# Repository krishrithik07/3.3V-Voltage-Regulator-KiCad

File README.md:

# 3.3V Voltage Regulator Circuit

**KiCad | AP2112K-3.3 | Power Supply Design**

## Project Overview

This project involves designing a 3.3V voltage regulator circuit using the AP2112K-3.3 Low Dropout (LDO) regulator.

The circuit schematic includes input and output capacitors for power supply filtering and stable voltage regulation.

## Main Component

- AP2112K-3.3 – 3.3V LDO Voltage Regulator
- Input capacitors
- Output capacitors
- Power input and output connections

## Design Tools

- KiCad – Schematic Capture
- KiCad PCB Editor – PCB Layout (if completed)

## Design Progress

- [x] Schematic design
- [ ] Electrical Rule Check (ERC)
- [ ] Footprint assignment
- [ ] PCB layout
- [ ] Design Rule Check (DRC)
- [ ] Gerber generation
- [ ] Hardware testing

## Author

**Krishna Raj M**

Electronics and Communication Engineering

**Project Category:** PCB Design | Power Electronics

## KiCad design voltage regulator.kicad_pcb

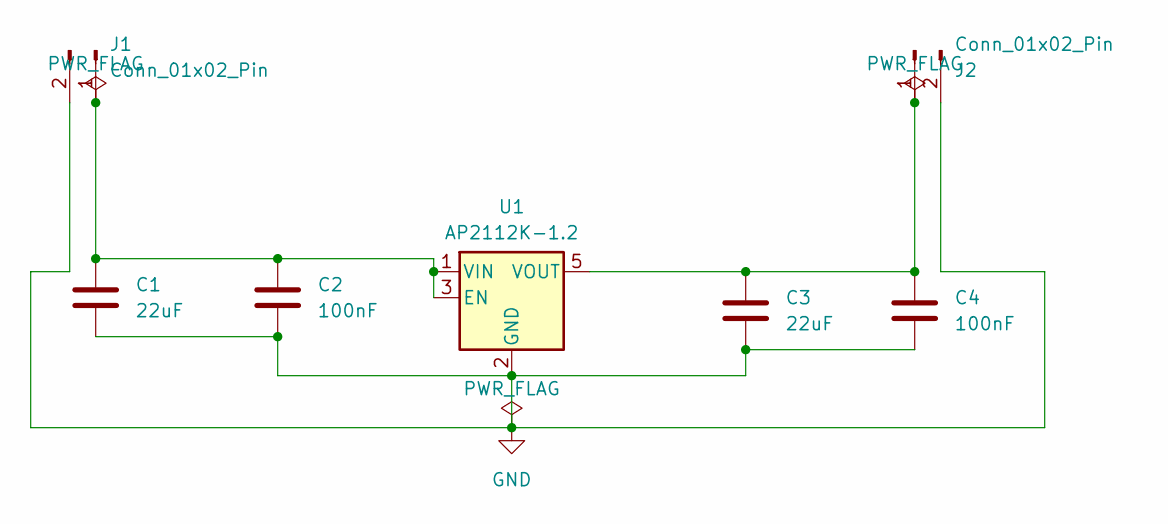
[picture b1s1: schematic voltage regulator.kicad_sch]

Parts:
C1, C3: 22uF; C_1206_3216Metric
C2, C4: 100nF; C_0805_2012Metric
J1, J2: Conn_01x02_Pin; PinHeader_1x02_P2.54mm_Vertical
U1: AP2112K-1.2; SOT-23-5

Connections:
GND: C1.2, C2.2, C3.2, C4.2, J1.2, J2.2, U1.2 (GND)
unnamed: C1.1, C2.1, J1.1, U1.1 (VIN), U1.3 (EN)
unnamed: C3.1, C4.1, J2.1, U1.5 (VOUT)

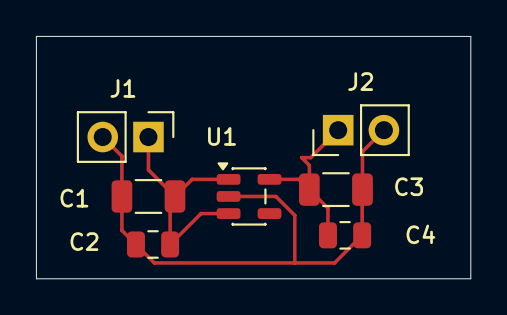
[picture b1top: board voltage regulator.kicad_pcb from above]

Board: 2 copper layers, 24.1 x 13.5 mm, 7 parts (0 on the bottom side), 3 nets.
